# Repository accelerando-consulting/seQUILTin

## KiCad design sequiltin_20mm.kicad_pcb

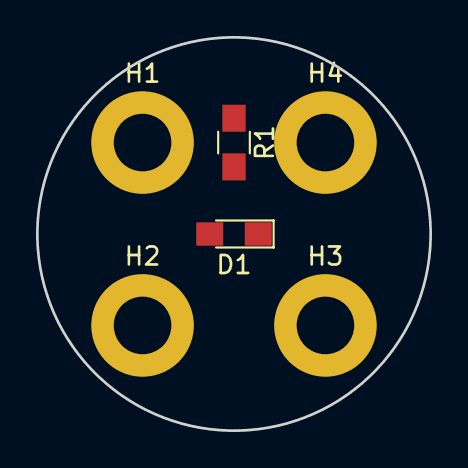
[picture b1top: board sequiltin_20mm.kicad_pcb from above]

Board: 2 copper layers, 21.8 x 21.8 mm, 6 parts (0 on the bottom side), 3 nets, no tracks yet.

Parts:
D1: LED; LED_0805_HandSoldering
H1, H2, H3, H4: MountingHole_Pad; MountingHole_3.2mm_M3_ISO7380_Pad
R1: R; R_0805_HandSoldering

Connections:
GND: D1.1, H2.1, H4.1
unnamed: D1.2, R1.2
VCC: H1.1, H3.1, R1.1

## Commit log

2018-11-19 Small sewable LED sequins for 0805 SMD LEDs
